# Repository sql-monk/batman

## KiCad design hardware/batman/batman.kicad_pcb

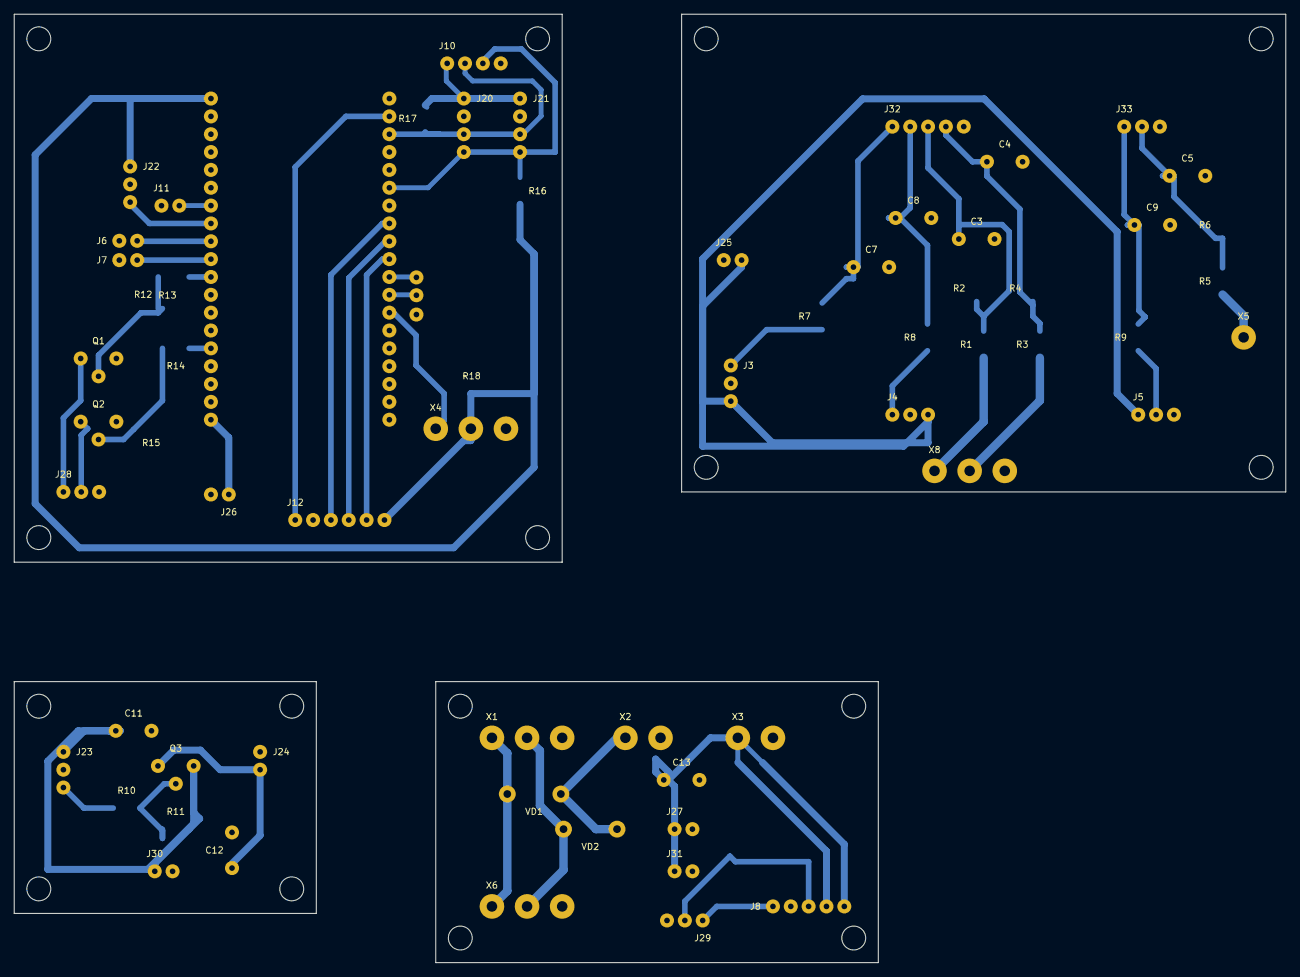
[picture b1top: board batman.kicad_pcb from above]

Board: 2 copper layers, 181.0 x 135.0 mm, 93 parts (0 on the bottom side), 37 nets.

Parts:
C3: 100n_50V; LUT_C3
C4: 100n_50V; LUT_C4
C5: 100n_50V; LUT_C5
C7: 1u_16V; LUT_C7
C8: 1u_16V; LUT_C8
C9: 1u_16V; LUT_C9
C11: 100n_16V; LUT_C11
C12: 100n_16V; LUT_C12
C13: 100n_16V; LUT_C13
HA1, HA2, HA3, HA4: M3_NPTH_3.4; Mount_M3
HB1, HB2, HB3, HB4: M3_NPTH_3.4; Mount_M3
HC1, HC2, HC3, HC4: M3_NPTH_3.4; Mount_M3
HD1, HD2, HD3, HD4: M3_NPTH_3.4; Mount_M3
J1: DevKitC_38_socket_mMCU; LUT_J1
J3: ACS1_3WIRE; LUT_J3
J4: ACS2_3WIRE; LUT_J4
J5: ACS3_3WIRE; LUT_J5
J6: SW1_GND_ON; LUT_J6
J7: SW2_GND_ON; LUT_J7
J8: RELAY; LUT_J8
J10: OLED_I2C; LUT_J10
J11: BUTTON; LUT_J11
J12: SPI; LUT_J12
J20: LINK_+3V3_GND_SCL_SDA; LUT_J20
J21: LINK_+3V3_GND_SCL_SDA; LUT_J21
J22: LINK_+3V3_GND_SENS_PWR; LUT_J22
J23: LINK_+3V3_GND_SENS_PWR; LUT_J23
J24: LINK_GND_+3V3_SENS; LUT_J24
J25: LINK_GND_+3V3_SENS; LUT_J25
J26: LINK_+5V_GND; LUT_J26
J27: LINK_+5V_GND; LUT_J27
J28: LINK_RELAY_IN1_RELAY_IN2_GND; LUT_J28
J29: LINK_RELAY_IN1_RELAY_IN2_GND; LUT_J29
J30: LINK_+3V3_GND; LUT_J30
J31: LINK_+5V_GND; LUT_J31
J32: LINK_I_B1_I_B2_U_B1_U_B2_GND; LUT_J32
J33: LINK_I_LOAD_U_LOAD_GND; LUT_J33
NT1: COPPER_STAR_AT_X3; LUT_NT1
Q1: BC547_CBE; LUT_Q1
Q2: BC547_CBE; LUT_Q2
Q3: BC557_CBE; LUT_Q3
R1: 100k_1%; LUT_R1
R2: 10k_1%; LUT_R2
R3: 100k_1%; LUT_R3
R4: 10k_1%; LUT_R4
R5: 100k_1%; LUT_R5
R6: 4.7k_1%; LUT_R6
R7: 1k; LUT_R7
R8: 1k; LUT_R8
R9: 1k; LUT_R9
R10: 4.7k; LUT_R10
R11: 10k; LUT_R11
R12: 1k; LUT_R12
R13: 10k; LUT_R13
R14: 1k; LUT_R14
R15: 10k; LUT_R15
R16: 4.7k; LUT_R16
R17: 4.7k; LUT_R17
R18: 4.7k; LUT_R18
VD1: 1N5819; LUT_VD1
VD2: 1N5819; LUT_VD2
WC2_1: EXTERNAL_CABLE_NOT_PCB; LUT_WC2_1
WC2_2: EXTERNAL_CABLE_NOT_PCB; LUT_WC2_2
WC2_3: EXTERNAL_CABLE_NOT_PCB; LUT_WC2_3
WC3_1: EXTERNAL_CABLE_NOT_PCB; LUT_WC3_1
WC3_2: EXTERNAL_CABLE_NOT_PCB; LUT_WC3_2
WC4_1: EXTERNAL_CABLE_NOT_PCB; LUT_WC4_1
WC4_2: EXTERNAL_CABLE_NOT_PCB; LUT_WC4_2
WC5_1: EXTERNAL_CABLE_NOT_PCB; LUT_WC5_1
WC5_2: EXTERNAL_CABLE_NOT_PCB; LUT_WC5_2
WC5_3: EXTERNAL_CABLE_NOT_PCB; LUT_WC5_3
WC6_1: EXTERNAL_CABLE_NOT_PCB; LUT_WC6_1
WC6_2: EXTERNAL_CABLE_NOT_PCB; LUT_WC6_2
WC6_3: EXTERNAL_CABLE_NOT_PCB; LUT_WC6_3
X1: B1_B2_GND; LUT_X1
X2: VIN_DC_GND; LUT_X2
X3: 5V_GND; LUT_X3
X4: DS18B20; LUT_X4
X5: U_LOAD_SENSE; LUT_X5
X6: BAT_SENSE_TO_B; LUT_X6
X8: BAT_SENSE_FROM_D; LUT_X8

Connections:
+3V3: C11.1, J1.1, J10.1, J12.6, J20.1, J21.1, J22.1, J23.1, J30.1, Q3.3, R11.2, R16.2, R17.2, R18.2, WC2_1.1, X4.2
+3V3_SENS: C12.1, J3.3, J4.3, J5.1, J24.2, J25.2, Q3.1, WC3_2.1
+5V: C13.1, J1.19, J26.1, J27.1, J31.1, NT1.1, WC4_1.1, X3.1
+5V_RELAY_COIL: J8.5, NT1.3
+5V_RELAY_VCC: J8.4, NT1.2
B1: R1.1, VD1.2, WC6_1.1, X1.1, X6.1, X8.1
B2: R3.1, VD2.2, WC6_2.1, X1.2, X6.2, X8.2
BASE1: Q1.2, R12.2, R13.1
BASE2: Q2.2, R14.2, R15.1
BASE3: Q3.2, R10.2, R11.1
BTN: J1.7, J11.2
CS: J1.29, J12.5
GND: C3.2, C4.2, C5.2, C7.2, C8.2, C9.2, C11.2, C12.2, C13.2, J1.14, J1.20, J1.26, J3.2, J4.2, J5.3, J6.1, J7.1, J8.2, J10.4, J11.1, J12.2, J20.2, J21.2, J22.2, J23.2, J24.1, J25.1, J26.2, J27.2, J28.3, J29.3, J30.2, J31.2, J32.5, J33.3, Q1.3, Q2.3, R2.2, R4.2, R6.2, R13.2, R15.2, WC2_2.1, WC3_1.1, WC4_2.1, WC5_3.1, WC6_3.1, X1.3, X2.2, X3.2, X4.3, X6.3, X8.3
I_B1: C7.1, J32.1, R7.2
I_B2: C8.1, J32.2, R8.2
I_LOAD: C9.1, J33.1, R9.2
I_RAW1: J3.1, R7.1
I_RAW2: J4.1, R8.1
I_RAW3: J5.2, R9.1
K1: J1.11, R12.1
K2: J1.15, R14.1
LOAD+: R5.1, X5.1
MISO: J1.27, J12.3
MOSI: J1.21, J12.1
OW: J1.32, R18.1, X4.1
RELAY_IN1: J8.1, J28.1, J29.1, Q1.1, WC5_1.1
RELAY_IN2: J8.3, J28.2, J29.2, Q2.1, WC5_2.1
SCK: J1.28, J12.4
SCL: J1.22, J10.2, J20.3, J21.3, R17.1
SDA: J1.25, J10.3, J20.4, J21.4, R16.1
SENS_PWR: J1.8, J22.3, J23.3, R10.1, WC2_3.1
SW1_ON: J1.9, J6.2
SW2_ON: J1.10, J7.2
U_B1: C3.1, J32.3, R1.2, R2.1
U_B2: C4.1, J32.4, R3.2, R4.1
U_LOAD: C5.1, J33.2, R5.2, R6.1
VIN_DC: VD1.1, VD2.1, X2.1

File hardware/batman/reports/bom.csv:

Reference,Documentation_alias,Value,Quantity,Location,Populate
J1,,DevKitC_38_socket_mMCU,1,A,yes
J2,,ADS1115_socket_mADC,1,A,yes
J3,,ACS1_3WIRE,1,A,yes
J4,,ACS2_3WIRE,1,A,yes
J5,,ACS3_3WIRE,1,A,yes
J6,,SW1_GND_ON,1,A,yes
J7,,SW2_GND_ON,1,A,yes
J8,,RELAY,1,A,yes
J9,,DPS_UART,1,A,yes
J10,,OLED_I2C,1,A,yes
J11,,BUTTON,1,A,yes
J12,,SPI,1,A,yes
X1,,B1_B2_GND,1,A,yes
X2,,VIN_DC_GND,1,A,yes
X3,,5V_GND,1,A,yes
X4,,DS18B20,1,A,yes
X5,,U_LOAD_SENSE,1,A,yes
NT1,,COPPER_STAR_AT_X3,1,A,copper only
VD1,,1N5819,1,A,yes
VD2,,1N5819,1,A,yes
R1,,100k_1%,1,A,yes
R2,,10k_1%,1,A,yes
C3,,100n_50V,1,A,yes
R3,,100k_1%,1,A,yes
R4,,10k_1%,1,A,yes
C4,,100n_50V,1,A,yes
R5,,100k_1%,1,A,yes
R6,,4.7k_1%,1,A,yes
C5,,100n_50V,1,A,yes
R7,,1k,1,A,yes
C7,,1u_16V,1,A,yes
R8,,1k,1,A,yes
C8,,1u_16V,1,A,yes
R9,,1k,1,A,yes
C9,,1u_16V,1,A,yes
C6,,100n_16V,1,A,yes
R10,,4.7k,1,A,yes
R11,,10k,1,A,yes
Q3,,BC557_CBE,1,A,yes
R12,,1k,1,A,yes
R13,,10k,1,A,yes
Q1,,BC547_CBE,1,A,yes
R14,,1k,1,A,yes
R15,,10k,1,A,yes
Q2,,BC547_CBE,1,A,yes
R16,,4.7k,1,A,yes
R17,,4.7k,1,A,yes
R18,,4.7k,1,A,yes
XLP1,XLP,LOAD_P06_P12_P13,1,external,yes
XGND1,XGND,GND_P24_P25_P26_P27_P28,1,external,yes
C1,,100u_50V_ALUMINIUM,1,external,yes
C2,,100n_50V,1,external,yes
D3,,1.5KE33A_DNP,1,external,DNP
XB1,,BAT1_PANEL,1,external,yes
F1,,ATO_15A,1,external,yes
mACS1,,ACS711EX_15.5A,1,external,yes
mSW1,,Pololu_2815_HP,1,external,yes
mDIO1,,XL74610,1,external,yes
XB2,,BAT2_PANEL,1,external,yes
F2,,ATO_15A,1,external,yes
mACS2,,ACS711EX_15.5A,1,external,yes
mSW2,,Pololu_2815_HP,1,external,yes
mDIO2,,XL74610,1,external,yes
mACS3,,ACS711EX_15.5A,1,external,yes
Fout1,Fout,ATO_15A,1,external,yes
XLOAD1,XLOAD,LOAD_PANEL,1,external,yes
XPSU1,XPSU,PSU_33V_10A_PANEL,1,external,yes
mDPS1,mDPS,DPS5015_9600_8N1_ADDR1,1,external,yes
Fchg1,Fchg,ATO_15A,1,external,yes
mDIO3,,XL74610,1,external,yes
mREL2,,FL_3FF_5V_10A_REMOVE_JUMPER,1,external,yes
mDC5,,LM2596_SET_5.0V_FIRST,1,external,yes
mOLED1,mOLED,SSD1306_0x3C,1,external,yes
T1,,DS18B20_PROBE,1,external,yes
T2,,DS18B20_PROBE,1,external,yes
SW1,,PANEL_BUTTON_NO,1,external,yes

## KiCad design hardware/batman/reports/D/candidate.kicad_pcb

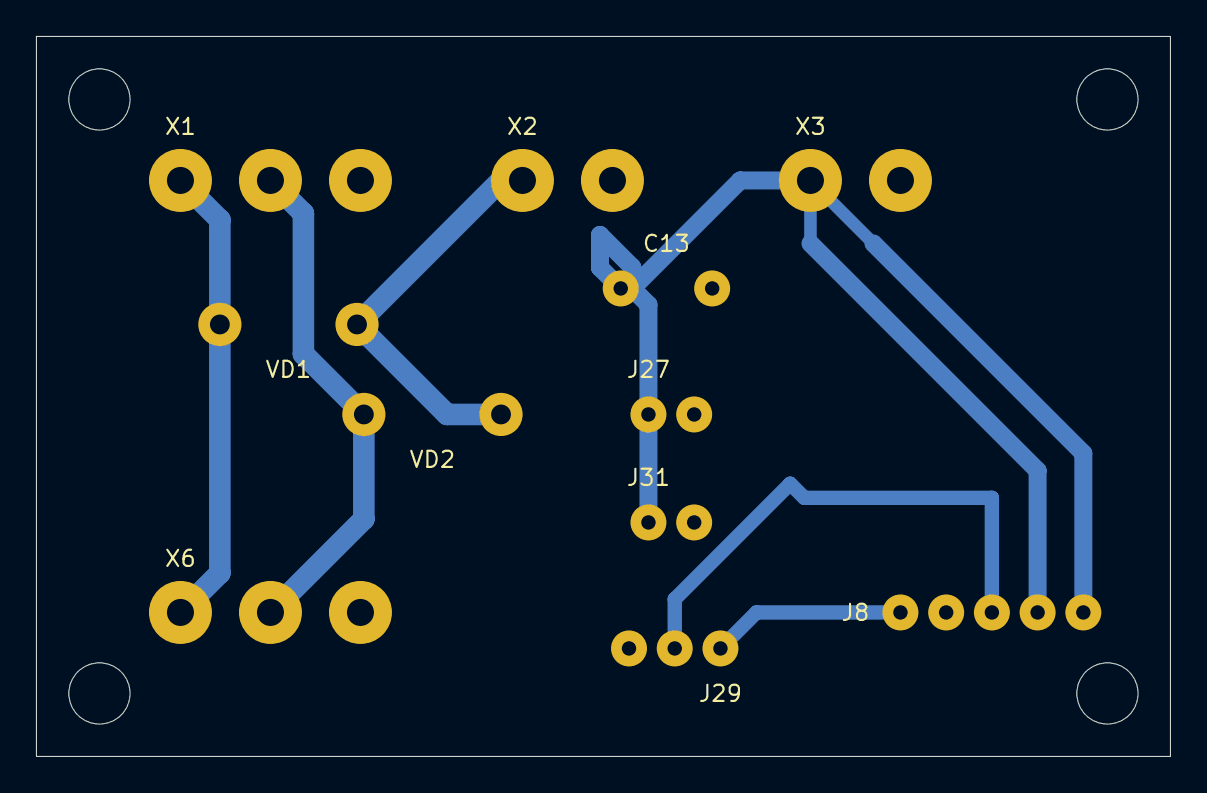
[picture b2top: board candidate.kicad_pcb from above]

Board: 2 copper layers, 63.0 x 40.0 mm, 16 parts (0 on the bottom side), 9 nets.

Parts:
C13: 100n_16V; LUT_C13
HD1, HD2, HD3, HD4: M3_NPTH_3.4; Mount_M3
J8: RELAY; LUT_J8
J27: LINK_+5V_GND; LUT_J27
J29: LINK_RELAY_IN1_RELAY_IN2_GND; LUT_J29
J31: LINK_+5V_GND; LUT_J31
NT1: COPPER_STAR_AT_X3; LUT_NT1
VD1: 1N5819; LUT_VD1
VD2: 1N5819; LUT_VD2
X1: B1_B2_GND; LUT_X1
X2: VIN_DC_GND; LUT_X2
X3: 5V_GND; LUT_X3
X6: BAT_SENSE_TO_B; LUT_X6

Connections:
+5V: C13.1, J27.1, J31.1, NT1.1, X3.1
+5V_RELAY_COIL: J8.5, NT1.3
+5V_RELAY_VCC: J8.4, NT1.2
B1: VD1.2, X1.1, X6.1
B2: VD2.2, X1.2, X6.2
GND: C13.2, J8.2, J27.2, J29.3, J31.2, X1.3, X2.2, X3.2, X6.3
RELAY_IN1: J8.1, J29.1
RELAY_IN2: J8.3, J29.2
VIN_DC: VD1.1, VD2.1, X2.1
